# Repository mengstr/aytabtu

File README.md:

# AYTABTU

**[All Your Transistors Are Belong to Us] - A computer built from discrete parts**

This is my attempt of building a complete computer using only discrete parts like transistors, diodes, capactitors and resistors.

Just to get warmed up a bit I've started designing an UART capable of transmiting and receiving serial data in 300 bps.

I plan to make proper PCBs for the boards that I require a lot of, like memory, registers and ALU-slices, but many of the more or less one-off boards will be made on standard donut-perfboard with thru-hole parts.

## Credits
I've used, collected, gleaned, stolen, borrowed and been inspired by the information on the following web sites:

Donut pcb layout creator - [code.google.com/p/diy-layout-creator/](https://code.google.com/p/diy-layout-creator/)  
Ring counter - [vk2zay.net/article/201](http://www.vk2zay.net/article/201)  
Asymetric multivibrator - [4qdtec.com/mvibs.html](http://www.4qdtec.com/mvibs.html)  
Single cycle CPU - [eecg.toronto.edu/~moshovos/ECE243-07/...](http://www.eecg.toronto.edu/~moshovos/ECE243-07/l19-implemenation-single-cycle.html)  
Binary incrementer - [letslearncomputing.blogspot.com/2013/....](http://letslearncomputing.blogspot.com/2013/03/digital-logic-4-bit-binary-incrementer.html)  
12/8bit cpu - [usti8bit.blogspot.com](usti8bit.blogspot.com/2015_03_01_archive.html)  
8bit ttl cpu - [digitarworld.uw.hu/ttlcpu.html](http://digitarworld.uw.hu/ttlcpu.html)  
ASAP3 Computer - [pong74ls.blogspot.com/...](http://pong74ls.blogspot.com/2013/11/asap-3-almost-simple-as-possible.html)  
Tiny Tim - [northdownfarm.co.uk/rory/tim/tinytim.htm](http://www.northdownfarm.co.uk/rory/tim/tinytim.htm) 

## Links to my own resources
Link to Google Sheets for a [TX faker generator](https://docs.google.com/spreadsheets/d/1nLxUwCidM7_CYKXSP2XA_T4spadFk9zQSKAtxVXUBSM/edit?usp=sharing).

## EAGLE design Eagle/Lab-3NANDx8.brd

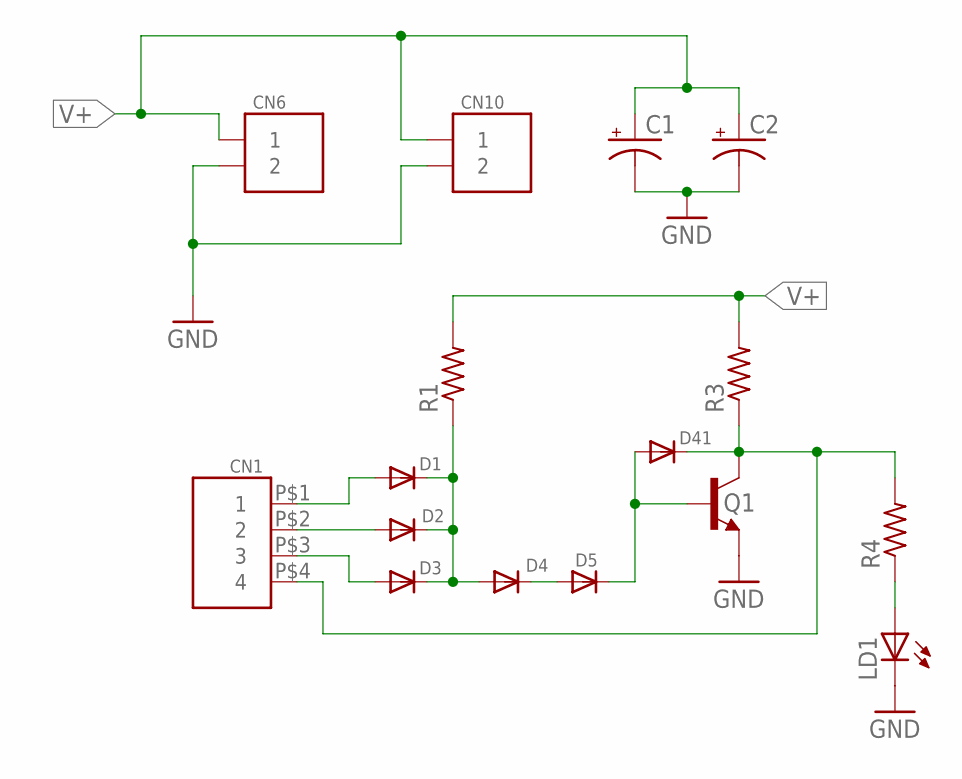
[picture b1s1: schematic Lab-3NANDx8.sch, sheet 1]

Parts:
C1, C2: CPOL-USE2.5-5; E2,5-5
CN1: HD4
CN6, CN10: HD2
D1, D2, D3, D4, D5: DIODE-6.3; DO35-6.3
D41: DIODE-7.6; DO35-7.6
LD1: LED3MM; 3MM
Q1: 2N3904-1; TO92BH
R1, R3, R4: R1/8-7.6MM; R0125-7.6

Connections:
GND: C1.-, C2.-, CN6.P$2 (2), CN10.P$2 (2), LD1.C, Q1.1 (E); also elsewhere on the board
unnamed: CN1.P$1 (1), D1.A
unnamed: CN1.P$2 (2), D2.A
unnamed: CN1.P$3 (3), D3.A
unnamed: D1.C, D2.C, D3.C, D4.A, R1.1
unnamed: D4.C, D5.A
unnamed: D5.C, D41.A, Q1.2 (B)
unnamed: LD1.A, R4.1
unnamed: CN1.P$4 (4), D41.C, Q1.3 (C), R3.1, R4.2
V+: C1.+, C2.+, CN6.P$1 (1), CN10.P$1 (1), R1.2, R3.2; also elsewhere on the board

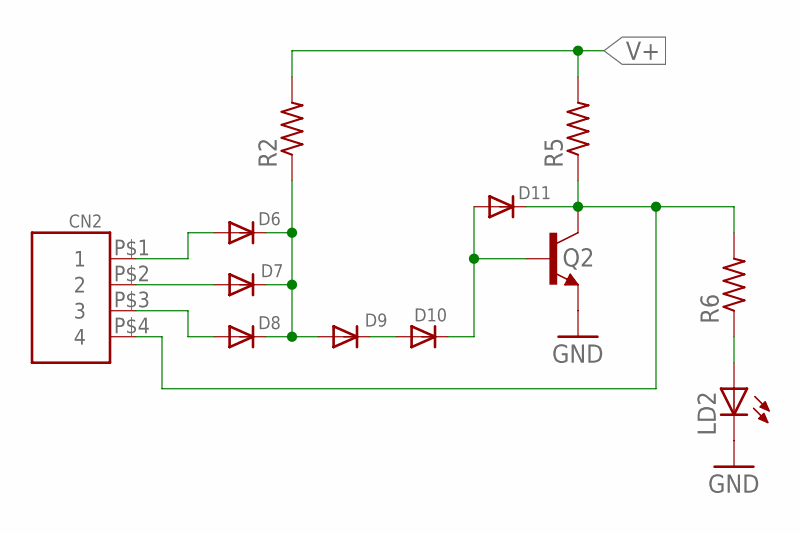
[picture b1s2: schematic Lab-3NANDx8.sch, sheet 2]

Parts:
CN2: HD4
D6, D7, D8, D9, D10: DIODE-6.3; DO35-6.3
D11: DIODE-7.6; DO35-7.6
LD2: LED3MM; 3MM
Q2: 2N3904-1; TO92BH
R2, R5, R6: R1/8-7.6MM; R0125-7.6

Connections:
GND: LD2.C, Q2.1 (E); also elsewhere on the board
unnamed: CN2.P$1 (1), D6.A
unnamed: CN2.P$2 (2), D7.A
unnamed: CN2.P$3 (3), D8.A
unnamed: D6.C, D7.C, D8.C, D9.A, R2.1
unnamed: D9.C, D10.A
unnamed: D10.C, D11.A, Q2.2 (B)
unnamed: CN2.P$4 (4), D11.C, Q2.3 (C), R5.1, R6.2
unnamed: LD2.A, R6.1
V+: R2.2, R5.2; also elsewhere on the board

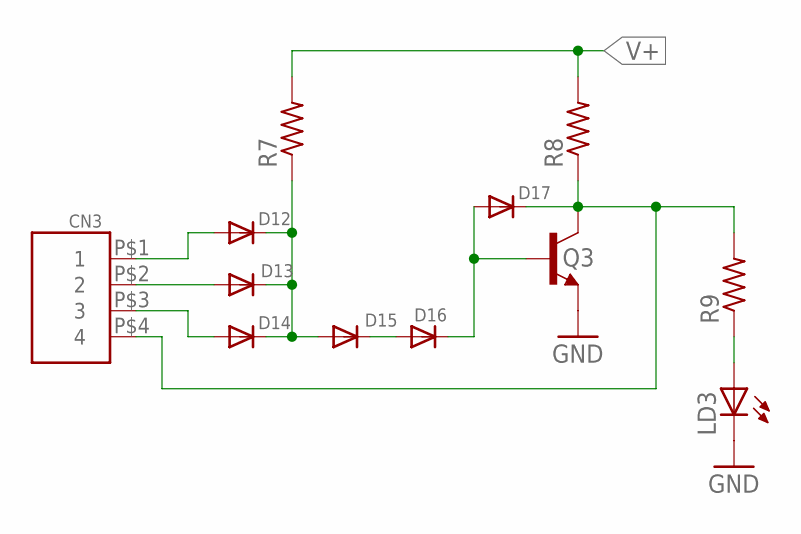
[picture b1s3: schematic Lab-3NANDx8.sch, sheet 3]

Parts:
CN3: HD4
D12, D13, D14, D15, D16: DIODE-6.3; DO35-6.3
D17: DIODE-7.6; DO35-7.6
LD3: LED3MM; 3MM
Q3: 2N3904-1; TO92BH
R7, R8, R9: R1/8-7.6MM; R0125-7.6

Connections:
GND: LD3.C, Q3.1 (E); also elsewhere on the board
unnamed: CN3.P$1 (1), D12.A
unnamed: CN3.P$2 (2), D13.A
unnamed: CN3.P$3 (3), D14.A
unnamed: D12.C, D13.C, D14.C, D15.A, R7.1
unnamed: D15.C, D16.A
unnamed: D16.C, D17.A, Q3.2 (B)
unnamed: CN3.P$4 (4), D17.C, Q3.3 (C), R8.1, R9.2
unnamed: LD3.A, R9.1
V+: R7.2, R8.2; also elsewhere on the board

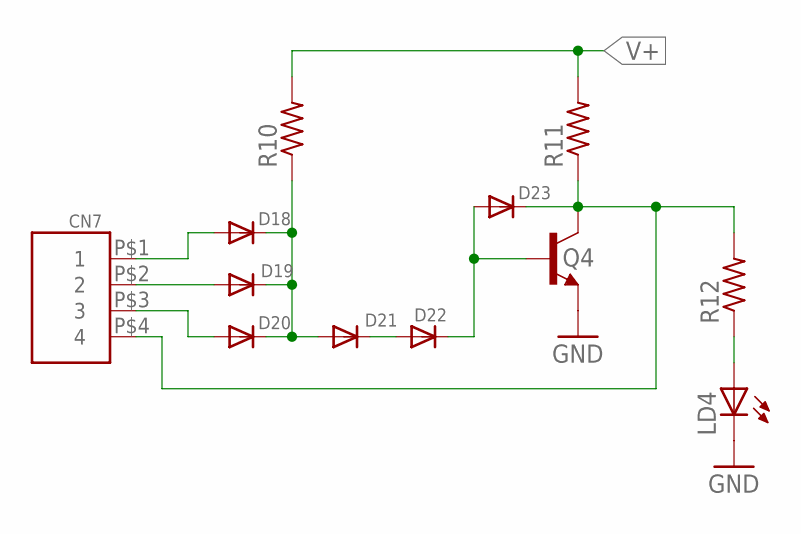
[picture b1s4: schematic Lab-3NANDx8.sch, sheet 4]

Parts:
CN7: HD4
D18, D19, D20, D21, D22: DIODE-6.3; DO35-6.3
D23: DIODE-7.6; DO35-7.6
LD4: LED3MM; 3MM
Q4: 2N3904-1; TO92BH
R10, R11, R12: R1/8-7.6MM; R0125-7.6

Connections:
GND: LD4.C, Q4.1 (E); also elsewhere on the board
unnamed: CN7.P$1 (1), D18.A
unnamed: CN7.P$2 (2), D19.A
unnamed: CN7.P$3 (3), D20.A
unnamed: D18.C, D19.C, D20.C, D21.A, R10.1
unnamed: D21.C, D22.A
unnamed: D22.C, D23.A, Q4.2 (B)
unnamed: CN7.P$4 (4), D23.C, Q4.3 (C), R11.1, R12.2
unnamed: LD4.A, R12.1
V+: R10.2, R11.2; also elsewhere on the board

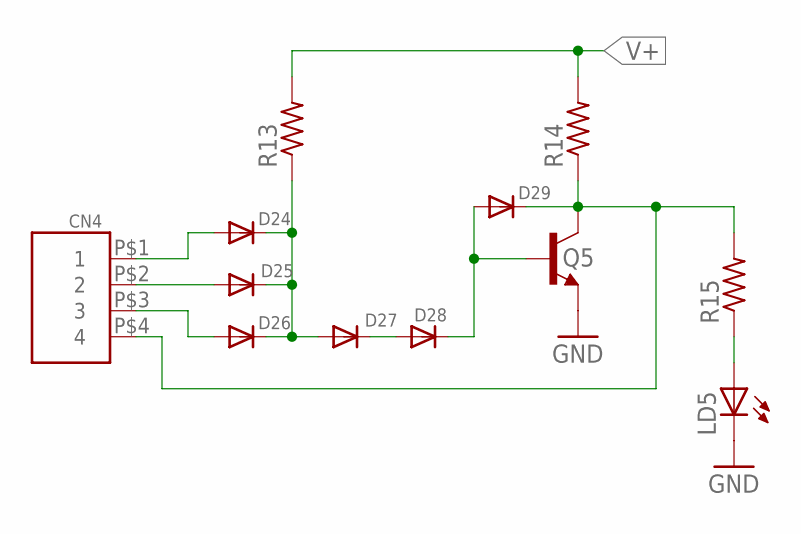
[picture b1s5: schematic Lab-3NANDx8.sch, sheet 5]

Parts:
CN4: HD4
D24, D25, D26, D27, D28: DIODE-6.3; DO35-6.3
D29: DIODE-7.6; DO35-7.6
LD5: LED3MM; 3MM
Q5: 2N3904-1; TO92BH
R13, R14, R15: R1/8-7.6MM; R0125-7.6

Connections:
GND: LD5.C, Q5.1 (E); also elsewhere on the board
unnamed: CN4.P$1 (1), D24.A
unnamed: CN4.P$2 (2), D25.A
unnamed: CN4.P$3 (3), D26.A
unnamed: D24.C, D25.C, D26.C, D27.A, R13.1
unnamed: D27.C, D28.A
unnamed: D28.C, D29.A, Q5.2 (B)
unnamed: CN4.P$4 (4), D29.C, Q5.3 (C), R14.1, R15.2
unnamed: LD5.A, R15.1
V+: R13.2, R14.2; also elsewhere on the board

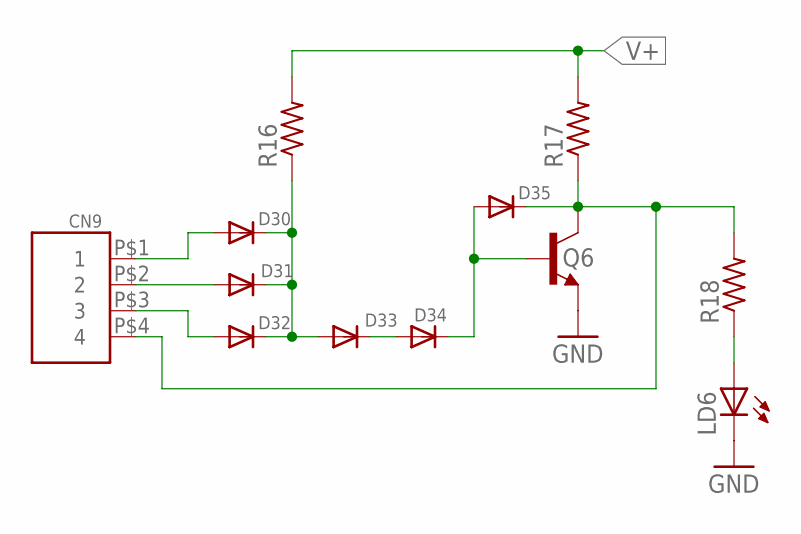
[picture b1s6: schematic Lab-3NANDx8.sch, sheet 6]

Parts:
CN9: HD4
D30, D31, D32, D33, D34: DIODE-6.3; DO35-6.3
D35: DIODE-7.6; DO35-7.6
LD6: LED3MM; 3MM
Q6: 2N3904-1; TO92BH
R16, R17, R18: R1/8-7.6MM; R0125-7.6

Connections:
GND: LD6.C, Q6.1 (E); also elsewhere on the board
unnamed: CN9.P$1 (1), D30.A
unnamed: CN9.P$2 (2), D31.A
unnamed: CN9.P$3 (3), D32.A
unnamed: D30.C, D31.C, D32.C, D33.A, R16.1
unnamed: D33.C, D34.A
unnamed: D34.C, D35.A, Q6.2 (B)
unnamed: CN9.P$4 (4), D35.C, Q6.3 (C), R17.1, R18.2
unnamed: LD6.A, R18.1
V+: R16.2, R17.2; also elsewhere on the board

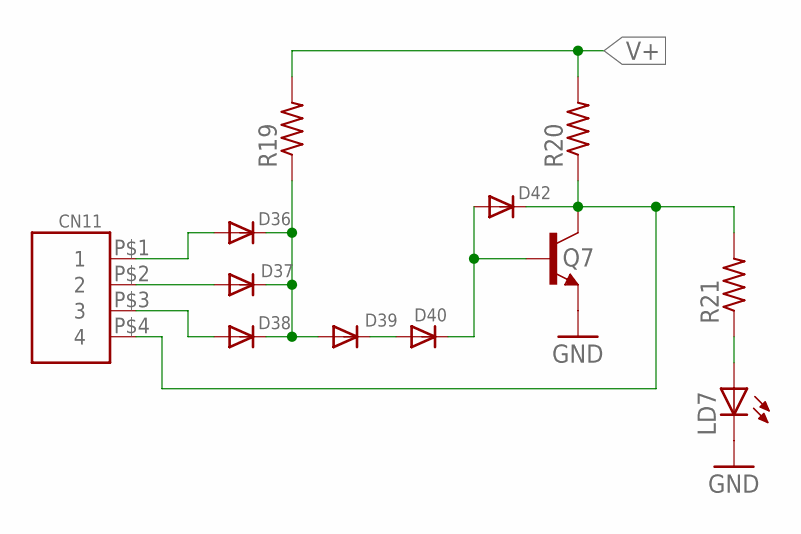
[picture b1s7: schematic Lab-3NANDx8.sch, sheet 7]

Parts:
CN11: HD4
D36, D37, D38, D39, D40: DIODE-6.3; DO35-6.3
D42: DIODE-7.6; DO35-7.6
LD7: LED3MM; 3MM
Q7: 2N3904-1; TO92BH
R19, R20, R21: R1/8-7.6MM; R0125-7.6

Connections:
GND: LD7.C, Q7.1 (E); also elsewhere on the board
unnamed: CN11.P$1 (1), D36.A
unnamed: CN11.P$2 (2), D37.A
unnamed: CN11.P$3 (3), D38.A
unnamed: D36.C, D37.C, D38.C, D39.A, R19.1
unnamed: D39.C, D40.A
unnamed: D40.C, D42.A, Q7.2 (B)
unnamed: CN11.P$4 (4), D42.C, Q7.3 (C), R20.1, R21.2
unnamed: LD7.A, R21.1
V+: R19.2, R20.2; also elsewhere on the board

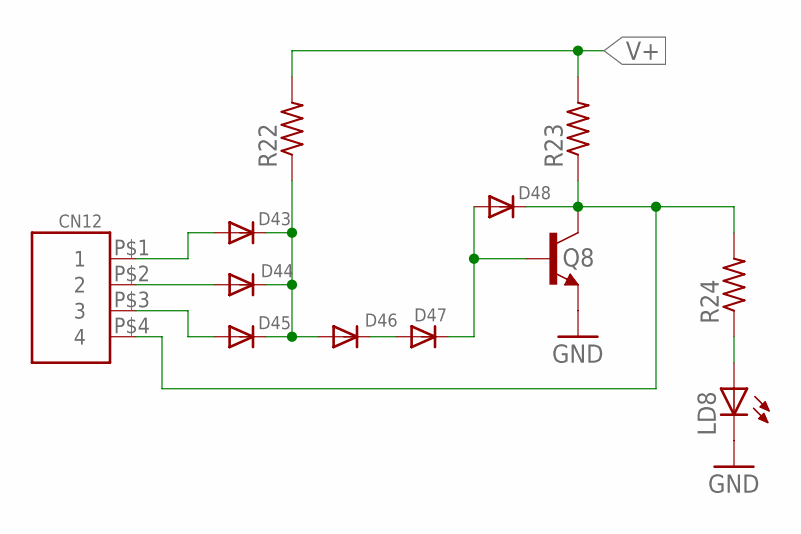
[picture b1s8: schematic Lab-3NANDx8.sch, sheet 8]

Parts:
CN12: HD4
D43, D44, D45, D46, D47: DIODE-6.3; DO35-6.3
D48: DIODE-7.6; DO35-7.6
LD8: LED3MM; 3MM
Q8: 2N3904-1; TO92BH
R22, R23, R24: R1/8-7.6MM; R0125-7.6

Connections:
GND: LD8.C, Q8.1 (E); also elsewhere on the board
unnamed: CN12.P$1 (1), D43.A
unnamed: CN12.P$2 (2), D44.A
unnamed: CN12.P$3 (3), D45.A
unnamed: D43.C, D44.C, D45.C, D46.A, R22.1
unnamed: D46.C, D47.A
unnamed: D47.C, D48.A, Q8.2 (B)
unnamed: CN12.P$4 (4), D48.C, Q8.3 (C), R23.1, R24.2
unnamed: LD8.A, R24.1
V+: R22.2, R23.2; also elsewhere on the board

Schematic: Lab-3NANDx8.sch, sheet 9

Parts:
CN5: HD4
D49, D50, D51, D52, D53: DIODE-6.3; DO35-6.3
D54: DIODE-7.6; DO35-7.6
LD9: LED3MM; 3MM
Q9: 2N3904-1; TO92BH
R25, R26, R27: R1/8-7.6MM; R0125-7.6

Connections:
GND: LD9.C, Q9.1 (E); also elsewhere on the board
unnamed: CN5.P$1 (1), D49.A
unnamed: CN5.P$2 (2), D50.A
unnamed: CN5.P$3 (3), D51.A
unnamed: D49.C, D50.C, D51.C, D52.A, R25.1
unnamed: D52.C, D53.A
unnamed: D53.C, D54.A, Q9.2 (B)
unnamed: CN5.P$4 (4), D54.C, Q9.3 (C), R26.1, R27.2
unnamed: LD9.A, R27.1
V+: R25.2, R26.2; also elsewhere on the board

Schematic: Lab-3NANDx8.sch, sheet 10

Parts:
CN14: HD4
D55, D56, D57, D58, D59: DIODE-6.3; DO35-6.3
D60: DIODE-7.6; DO35-7.6
LD10: LED3MM; 3MM
Q10: 2N3904-1; TO92BH
R28, R29, R30: R1/8-7.6MM; R0125-7.6

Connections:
GND: LD10.C, Q10.1 (E); also elsewhere on the board
unnamed: CN14.P$1 (1), D55.A
unnamed: CN14.P$2 (2), D56.A
unnamed: CN14.P$3 (3), D57.A
unnamed: D55.C, D56.C, D57.C, D58.A, R28.1
unnamed: D58.C, D59.A
unnamed: D59.C, D60.A, Q10.2 (B)
unnamed: CN14.P$4 (4), D60.C, Q10.3 (C), R29.1, R30.2
unnamed: LD10.A, R30.1
V+: R28.2, R29.2; also elsewhere on the board

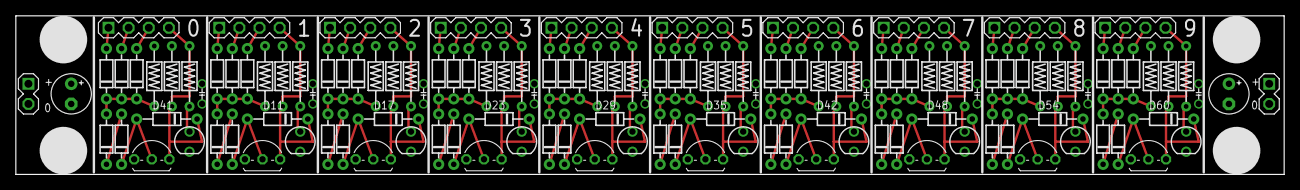
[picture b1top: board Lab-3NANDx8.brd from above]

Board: 2 copper layers, 160.0 x 20.0 mm, 124 parts (0 on the bottom side), 82 nets.

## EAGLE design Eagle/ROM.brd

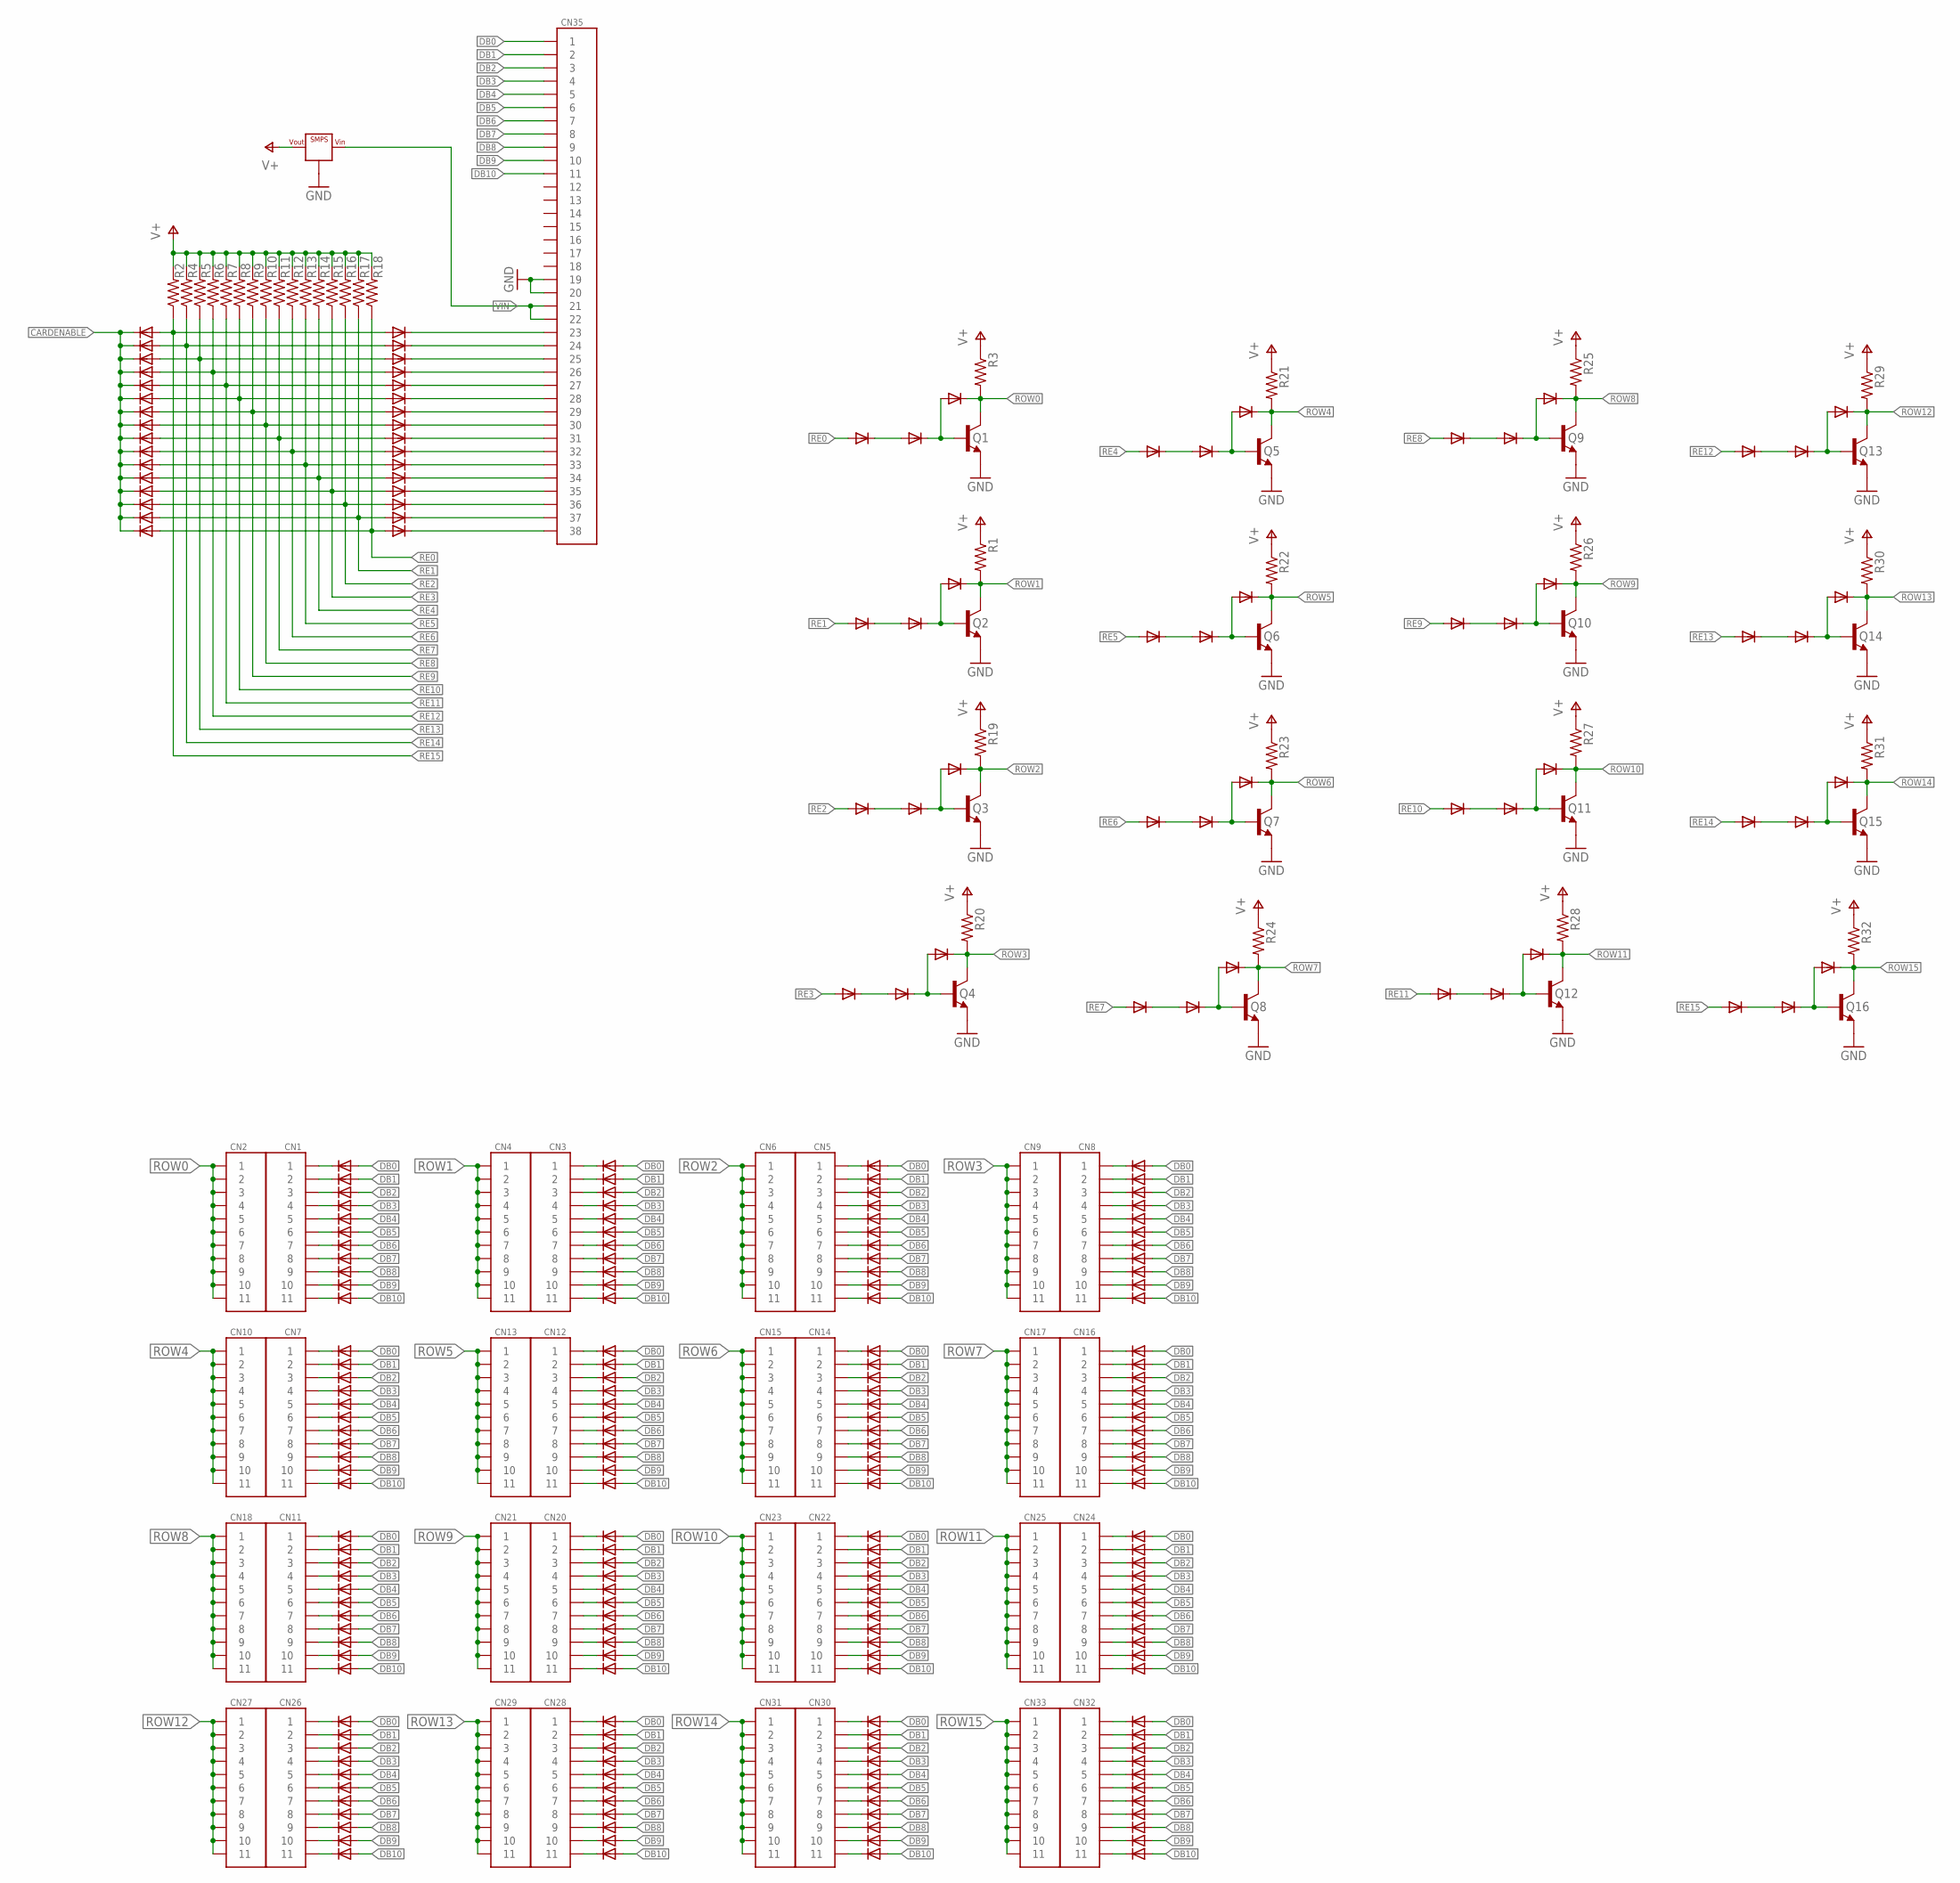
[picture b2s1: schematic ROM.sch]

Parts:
CN1, CN2, CN3, CN4, CN5, CN6, CN7, CN8, CN9, CN10, CN11, CN12, CN13, CN14, CN15, CN16, CN17, CN18, CN20, CN21, CN22, CN23, CN24, CN25, CN26, CN27, CN28, CN29, CN30, CN31, CN32, CN33: HD11
CN35: HD38-HP; HD38-HOLEPAD
D1, D2, D3, D4, D5, D6, D7, D8, D9, D10, D11, D12, D13, D14, D15, D16, D17, D18, D19, D20, D21, D22, D23, D24, D25, D26, D27, D28, D29, D30, D31, D32, D33, D34, D35, D36, D37, D38, D39, D40, D41, D42, D43, D44, D45, D46, D47, D48, D49, D50, D51, D52, D53, D54, D55, D56, D57, D58, D59, D60, D61, D62, D63, D64, D65, D66, D67, D68, D69, D70, D71, D72, D73, D74, D75, D76, D77, D78, D79, D80, D81, D82, D83, D84, D85, D86, D87, D88, D89, D90, D91, D92, D93, D94, D95, D96, D97, D98, D99, D100, D101, D102, D103, D104, D105, D106, D107, D108, D109, D110, D111, D112, D113, D114, D115, D116, D117, D118, D119, D120, D121, D122, D123, D124, D125, D126, D127, D128, D129, D130, D131, D132, D133, D134, D135, D136, D137, D138, D139, D140, D141, D142, D143, D144, D145, D146, D147, D148, D149, D150, D151, D152, D153, D154, D155, D156, D157, D158, D159, D160, D161, D162, D163, D164, D165, D166, D167, D168, D169, D170, D171, D172, D173, D174, D175, D176: DIODE-6.3; DO35-6.3
D177, D178, D179, D180, D181, D182, D183, D184, D185, D186, D187, D188, D189, D190, D191, D192, D193, D194, D195, D196, D197, D198, D199, D200, D201, D202, D203, D204, D205, D206, D207, D208, D209, D210, D211, D212, D213, D214, D215, D216, D217, D218, D219, D220, D221, D222, D223, D224, D225, D226, D227, D228, D229, D230, D231, D232, D233, D234, D235, D236, D237, D238, D239, D240, D241, D242, D243, D244, D245, D246, D247, D248, D249, D250, D251, D252, D253, D254, D255, D256: DIODE-5.08; DO35-5.08
Q1, Q2, Q3, Q4, Q5, Q6, Q7, Q8, Q9, Q10, Q11, Q12, Q13, Q14, Q15, Q16: BC547-STRAIGHT; TO92-S-CBE
R1, R2, R3, R4, R5, R6, R7, R8, R9, R10, R11, R12, R13, R14, R15, R16, R17, R18, R19, R20, R21, R22, R23, R24, R25, R26, R27, R28, R29, R30, R31, R32: R1/8-6MM; R0125-6.3
VR1: SMPS; BUCK1722

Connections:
CARDENABLE: D182.C, D183.C, D184.C, D185.C, D186.C, D187.C, D188.C, D189.C, D190.C, D191.C, D192.C, D193.C, D194.C, D195.C, D196.C, D197.C
DB0: CN35.P1@1 (1), CN35.P1@2 (1), D1.A, D12.A, D23.A, D34.A, D45.A, D56.A, D67.A, D78.A, D89.A, D100.A, D111.A, D122.A, D133.A, D144.A, D155.A, D166.A
DB1: CN35.P2@1 (2), CN35.P2@2 (2), D2.A, D13.A, D24.A, D35.A, D46.A, D57.A, D68.A, D79.A, D90.A, D101.A, D112.A, D123.A, D134.A, D145.A, D156.A, D167.A
DB2: CN35.P3@1 (3), CN35.P3@2 (3), D3.A, D14.A, D25.A, D36.A, D47.A, D58.A, D69.A, D80.A, D91.A, D102.A, D113.A, D124.A, D135.A, D146.A, D157.A, D168.A
DB3: CN35.P4@1 (4), CN35.P4@2 (4), D4.A, D15.A, D26.A, D37.A, D48.A, D59.A, D70.A, D81.A, D92.A, D103.A, D114.A, D125.A, D136.A, D147.A, D158.A, D169.A
DB4: CN35.P5@1 (5), CN35.P5@2 (5), D5.A, D16.A, D27.A, D38.A, D49.A, D60.A, D71.A, D82.A, D93.A, D104.A, D115.A, D126.A, D137.A, D148.A, D159.A, D170.A
DB5: CN35.P6@1 (6), CN35.P6@2 (6), D6.A, D17.A, D28.A, D39.A, D50.A, D61.A, D72.A, D83.A, D94.A, D105.A, D116.A, D127.A, D138.A, D149.A, D160.A, D171.A
DB6: CN35.P7@1 (7), CN35.P7@2 (7), D7.A, D18.A, D29.A, D40.A, D51.A, D62.A, D73.A, D84.A, D95.A, D106.A, D117.A, D128.A, D139.A, D150.A, D161.A, D172.A
DB7: CN35.P8@1 (8), CN35.P8@2 (8), D8.A, D19.A, D30.A, D41.A, D52.A, D63.A, D74.A, D85.A, D96.A, D107.A, D118.A, D129.A, D140.A, D151.A, D162.A, D173.A
DB8: CN35.P9@1 (9), CN35.P9@2 (9), D9.A, D20.A, D31.A, D42.A, D53.A, D64.A, D75.A, D86.A, D97.A, D108.A, D119.A, D130.A, D141.A, D152.A, D163.A, D174.A
DB9: CN35.P10@1 (10), CN35.P10@2 (10), D10.A, D21.A, D32.A, D43.A, D54.A, D65.A, D76.A, D87.A, D98.A, D109.A, D120.A, D131.A, D142.A, D153.A, D164.A, D175.A
DB10: CN35.P11@1 (11), CN35.P11@2 (11), D11.A, D22.A, D33.A, D44.A, D55.A, D66.A, D77.A, D88.A, D99.A, D110.A, D121.A, D132.A, D143.A, D154.A, D165.A, D176.A
GND: CN35.P19@1 (19), CN35.P19@2 (19), CN35.P20@1 (20), CN35.P20@2 (20), Q1.E, Q2.E, Q3.E, Q4.E, Q5.E, Q6.E, Q7.E, Q8.E, Q9.E, Q10.E, Q11.E, Q12.E, Q13.E, Q14.E, Q15.E, Q16.E, VR1.GND@1 (GND), VR1.GND@2 (GND), VR1.GND@3 (GND), VR1.GND@4 (GND)
unnamed: CN1.P$1 (1), D1.C
unnamed: CN1.P$2 (2), D2.C
unnamed: CN1.P$3 (3), D3.C
unnamed: CN1.P$4 (4), D4.C
unnamed: CN1.P$5 (5), D5.C
unnamed: CN1.P$6 (6), D6.C
unnamed: CN1.P$7 (7), D7.C
unnamed: CN1.P$8 (8), D8.C
unnamed: CN1.P$9 (9), D9.C
unnamed: CN1.P$10 (10), D10.C
unnamed: CN1.P$11 (11), D11.C
unnamed: CN3.P$1 (1), D12.C
unnamed: CN3.P$2 (2), D13.C
unnamed: CN3.P$3 (3), D14.C
unnamed: CN3.P$4 (4), D15.C
unnamed: CN3.P$5 (5), D16.C
unnamed: CN3.P$6 (6), D17.C
unnamed: CN3.P$7 (7), D18.C
unnamed: CN3.P$8 (8), D19.C
unnamed: CN3.P$9 (9), D20.C
unnamed: CN3.P$10 (10), D21.C
unnamed: CN3.P$11 (11), D22.C
unnamed: CN5.P$1 (1), D23.C
unnamed: CN5.P$2 (2), D24.C
unnamed: CN5.P$3 (3), D25.C
unnamed: CN5.P$4 (4), D26.C
unnamed: CN5.P$5 (5), D27.C
unnamed: CN5.P$6 (6), D28.C
unnamed: CN5.P$7 (7), D29.C
unnamed: CN5.P$8 (8), D30.C
unnamed: CN5.P$9 (9), D31.C
unnamed: CN5.P$10 (10), D32.C
unnamed: CN5.P$11 (11), D33.C
unnamed: CN8.P$1 (1), D34.C
unnamed: CN8.P$2 (2), D35.C
unnamed: CN8.P$3 (3), D36.C
unnamed: CN8.P$4 (4), D37.C
unnamed: CN8.P$5 (5), D38.C
unnamed: CN8.P$6 (6), D39.C
unnamed: CN8.P$7 (7), D40.C
unnamed: CN8.P$8 (8), D41.C
unnamed: CN8.P$9 (9), D42.C
unnamed: CN8.P$10 (10), D43.C
unnamed: CN8.P$11 (11), D44.C
unnamed: CN7.P$1 (1), D45.C
unnamed: CN7.P$2 (2), D46.C
unnamed: CN7.P$3 (3), D47.C
unnamed: CN7.P$4 (4), D48.C
unnamed: CN7.P$5 (5), D49.C
unnamed: CN7.P$6 (6), D50.C
unnamed: CN7.P$7 (7), D51.C
unnamed: CN7.P$8 (8), D52.C
unnamed: CN7.P$9 (9), D53.C
unnamed: CN7.P$10 (10), D54.C
unnamed: CN7.P$11 (11), D55.C
unnamed: CN12.P$1 (1), D56.C
unnamed: CN12.P$2 (2), D57.C
unnamed: CN12.P$3 (3), D58.C
unnamed: CN12.P$4 (4), D59.C
unnamed: CN12.P$5 (5), D60.C
unnamed: CN12.P$6 (6), D61.C
unnamed: CN12.P$7 (7), D62.C
unnamed: CN12.P$8 (8), D63.C
unnamed: CN12.P$9 (9), D64.C
unnamed: CN12.P$10 (10), D65.C
unnamed: CN12.P$11 (11), D66.C
unnamed: CN14.P$1 (1), D67.C
unnamed: CN14.P$2 (2), D68.C
unnamed: CN14.P$3 (3), D69.C
unnamed: CN14.P$4 (4), D70.C
unnamed: CN14.P$5 (5), D71.C
unnamed: CN14.P$6 (6), D72.C
unnamed: CN14.P$7 (7), D73.C
unnamed: CN14.P$8 (8), D74.C
unnamed: CN14.P$9 (9), D75.C
unnamed: CN14.P$10 (10), D76.C
unnamed: CN14.P$11 (11), D77.C
unnamed: CN16.P$1 (1), D78.C
unnamed: CN16.P$2 (2), D79.C
unnamed: CN16.P$3 (3), D80.C
unnamed: CN16.P$4 (4), D81.C
unnamed: CN16.P$5 (5), D82.C
unnamed: CN16.P$6 (6), D83.C
unnamed: CN16.P$7 (7), D84.C
unnamed: CN16.P$8 (8), D85.C
unnamed: CN16.P$9 (9), D86.C
unnamed: CN16.P$10 (10), D87.C
unnamed: CN16.P$11 (11), D88.C
unnamed: CN11.P$1 (1), D89.C
unnamed: CN11.P$2 (2), D90.C
unnamed: CN11.P$3 (3), D91.C
unnamed: CN11.P$4 (4), D92.C
unnamed: CN11.P$5 (5), D93.C
unnamed: CN11.P$6 (6), D94.C
unnamed: CN11.P$7 (7), D95.C
unnamed: CN11.P$8 (8), D96.C
unnamed: CN11.P$9 (9), D97.C
unnamed: CN11.P$10 (10), D98.C
unnamed: CN11.P$11 (11), D99.C
unnamed: CN20.P$1 (1), D100.C
unnamed: CN20.P$2 (2), D101.C
unnamed: CN20.P$3 (3), D102.C
unnamed: CN20.P$4 (4), D103.C
unnamed: CN20.P$5 (5), D104.C
unnamed: CN20.P$6 (6), D105.C
unnamed: CN20.P$7 (7), D106.C
unnamed: CN20.P$8 (8), D107.C
unnamed: CN20.P$9 (9), D108.C
unnamed: CN20.P$10 (10), D109.C
unnamed: CN20.P$11 (11), D110.C
unnamed: CN22.P$1 (1), D111.C
unnamed: CN22.P$2 (2), D112.C
unnamed: CN22.P$3 (3), D113.C
unnamed: CN22.P$4 (4), D114.C
unnamed: CN22.P$5 (5), D115.C
unnamed: CN22.P$6 (6), D116.C
unnamed: CN22.P$7 (7), D117.C
unnamed: CN22.P$8 (8), D118.C
unnamed: CN22.P$9 (9), D119.C
unnamed: CN22.P$10 (10), D120.C
unnamed: CN22.P$11 (11), D121.C
unnamed: CN24.P$1 (1), D122.C
unnamed: CN24.P$2 (2), D123.C
unnamed: CN24.P$3 (3), D124.C
unnamed: CN24.P$4 (4), D125.C
unnamed: CN24.P$5 (5), D126.C
unnamed: CN24.P$6 (6), D127.C
unnamed: CN24.P$7 (7), D128.C
unnamed: CN24.P$8 (8), D129.C
unnamed: CN24.P$9 (9), D130.C
unnamed: CN24.P$10 (10), D131.C
unnamed: CN24.P$11 (11), D132.C
unnamed: CN26.P$1 (1), D133.C
unnamed: CN26.P$2 (2), D134.C
unnamed: CN26.P$3 (3), D135.C
unnamed: CN26.P$4 (4), D136.C
unnamed: CN26.P$5 (5), D137.C
unnamed: CN26.P$6 (6), D138.C
unnamed: CN26.P$7 (7), D139.C
unnamed: CN26.P$8 (8), D140.C
unnamed: CN26.P$9 (9), D141.C
unnamed: CN26.P$10 (10), D142.C
unnamed: CN26.P$11 (11), D143.C
unnamed: CN28.P$1 (1), D144.C
unnamed: CN28.P$2 (2), D145.C
unnamed: CN28.P$3 (3), D146.C
unnamed: CN28.P$4 (4), D147.C
unnamed: CN28.P$5 (5), D148.C
unnamed: CN28.P$6 (6), D149.C
unnamed: CN28.P$7 (7), D150.C
unnamed: CN28.P$8 (8), D151.C
unnamed: CN28.P$9 (9), D152.C
unnamed: CN28.P$10 (10), D153.C
unnamed: CN28.P$11 (11), D154.C
unnamed: CN30.P$1 (1), D155.C
unnamed: CN30.P$2 (2), D156.C
unnamed: CN30.P$3 (3), D157.C
unnamed: CN30.P$4 (4), D158.C
unnamed: CN30.P$5 (5), D159.C
unnamed: CN30.P$6 (6), D160.C
unnamed: CN30.P$7 (7), D161.C
unnamed: CN30.P$8 (8), D162.C
unnamed: CN30.P$9 (9), D163.C
unnamed: CN30.P$10 (10), D164.C
unnamed: CN30.P$11 (11), D165.C
unnamed: CN32.P$1 (1), D166.C
unnamed: CN32.P$2 (2), D167.C
unnamed: CN32.P$3 (3), D168.C
unnamed: CN32.P$4 (4), D169.C
unnamed: CN32.P$5 (5), D170.C
unnamed: CN32.P$6 (6), D171.C
unnamed: CN32.P$7 (7), D172.C
unnamed: CN32.P$8 (8), D173.C
unnamed: CN32.P$9 (9), D174.C
unnamed: CN32.P$10 (10), D175.C
unnamed: CN32.P$11 (11), D176.C
unnamed: D215.A, D216.C
unnamed: D177.C, D181.A, Q1.B
unnamed: D177.A, D178.C
unnamed: D212.C, D214.A, Q2.B
unnamed: D212.A, D213.C
unnamed: D215.C, D217.A, Q3.B
unnamed: D242.A, D243.C
unnamed: D218.C, D220.A, Q4.B
unnamed: D218.A, D219.C
unnamed: D221.C, D223.A, Q5.B
unnamed: D221.A, D222.C
unnamed: D224.C, D226.A, Q6.B
unnamed: D224.A, D225.C
unnamed: D227.C, D229.A, Q7.B
unnamed: D227.A, D228.C
unnamed: D230.C, D232.A, Q8.B
unnamed: D230.A, D231.C
unnamed: D233.C, D235.A, Q9.B
unnamed: D233.A, D234.C
unnamed: D236.C, D238.A, Q10.B
unnamed: D239.C, D241.A, Q11.B
unnamed: D239.A, D240.C
unnamed: D242.C, D244.A, Q12.B
unnamed: D251.A, D252.C
unnamed: D245.C, D247.A, Q13.B
unnamed: D236.A, D237.C
unnamed: D248.C, D250.A, Q14.B
unnamed: D245.A, D246.C
unnamed: D251.C, D253.A, Q15.B
unnamed: D248.A, D249.C
unnamed: D254.C, D256.A, Q16.B
unnamed: D254.A, D255.C
RE0: D178.A, D197.A, D211.A, R18.1
RE1: D196.A, D210.A, D213.A, R17.1
RE2: D195.A, D209.A, D216.A, R16.1
RE3: D194.A, D208.A, D219.A, R15.1
RE4: D193.A, D207.A, D222.A, R14.1
RE5: D192.A, D206.A, D225.A, R13.1
RE6: D191.A, D205.A, D228.A, R12.1
RE7: D190.A, D204.A, D231.A, R11.1
RE8: D189.A, D203.A, D234.A, R10.1
RE9: D188.A, D202.A, D237.A, R9.1
RE10: D187.A, D201.A, D240.A, R8.1
RE11: D186.A, D200.A, D243.A, R7.1
RE12: D185.A, D199.A, D246.A, R6.1
RE13: D184.A, D198.A, D249.A, R5.1
RE14: D180.A, D183.A, D252.A, R4.1
RE15: D179.A, D182.A, D255.A, R2.1
ROW0: CN2.P$1 (1), CN2.P$2 (2), CN2.P$3 (3), CN2.P$4 (4), CN2.P$5 (5), CN2.P$6 (6), CN2.P$7 (7), CN2.P$8 (8), CN2.P$9 (9), CN2.P$10 (10), CN2.P$11 (11), D181.C, Q1.C, R3.2
ROW1: CN4.P$1 (1), CN4.P$2 (2), CN4.P$3 (3), CN4.P$4 (4), CN4.P$5 (5), CN4.P$6 (6), CN4.P$7 (7), CN4.P$8 (8), CN4.P$9 (9), CN4.P$10 (10), CN4.P$11 (11), D214.C, Q2.C, R1.2
ROW2: CN6.P$1 (1), CN6.P$2 (2), CN6.P$3 (3), CN6.P$4 (4), CN6.P$5 (5), CN6.P$6 (6), CN6.P$7 (7), CN6.P$8 (8), CN6.P$9 (9), CN6.P$10 (10), CN6.P$11 (11), D217.C, Q3.C, R19.2
ROW3: CN9.P$1 (1), CN9.P$2 (2), CN9.P$3 (3), CN9.P$4 (4), CN9.P$5 (5), CN9.P$6 (6), CN9.P$7 (7), CN9.P$8 (8), CN9.P$9 (9), CN9.P$10 (10), CN9.P$11 (11), D220.C, Q4.C, R20.2
ROW4: CN10.P$1 (1), CN10.P$2 (2), CN10.P$3 (3), CN10.P$4 (4), CN10.P$5 (5), CN10.P$6 (6), CN10.P$7 (7), CN10.P$8 (8), CN10.P$9 (9), CN10.P$10 (10), CN10.P$11 (11), D223.C, Q5.C, R21.2
ROW5: CN13.P$1 (1), CN13.P$2 (2), CN13.P$3 (3), CN13.P$4 (4), CN13.P$5 (5), CN13.P$6 (6), CN13.P$7 (7), CN13.P$8 (8), CN13.P$9 (9), CN13.P$10 (10), CN13.P$11 (11), D226.C, Q6.C, R22.2
ROW6: CN15.P$1 (1), CN15.P$2 (2), CN15.P$3 (3), CN15.P$4 (4), CN15.P$5 (5), CN15.P$6 (6), CN15.P$7 (7), CN15.P$8 (8), CN15.P$9 (9), CN15.P$10 (10), CN15.P$11 (11), D229.C, Q7.C, R23.2
ROW7: CN17.P$1 (1), CN17.P$2 (2), CN17.P$3 (3), CN17.P$4 (4), CN17.P$5 (5), CN17.P$6 (6), CN17.P$7 (7), CN17.P$8 (8), CN17.P$9 (9), CN17.P$10 (10), CN17.P$11 (11), D232.C, Q8.C, R24.2
ROW8: CN18.P$1 (1), CN18.P$2 (2), CN18.P$3 (3), CN18.P$4 (4), CN18.P$5 (5), CN18.P$6 (6), CN18.P$7 (7), CN18.P$8 (8), CN18.P$9 (9), CN18.P$10 (10), CN18.P$11 (11), D235.C, Q9.C, R25.2
ROW9: CN21.P$1 (1), CN21.P$2 (2), CN21.P$3 (3), CN21.P$4 (4), CN21.P$5 (5), CN21.P$6 (6), CN21.P$7 (7), CN21.P$8 (8), CN21.P$9 (9), CN21.P$10 (10), CN21.P$11 (11), D238.C, Q10.C, R26.2
ROW10: CN23.P$1 (1), CN23.P$2 (2), CN23.P$3 (3), CN23.P$4 (4), CN23.P$5 (5), CN23.P$6 (6), CN23.P$7 (7), CN23.P$8 (8), CN23.P$9 (9), CN23.P$10 (10), CN23.P$11 (11), D241.C, Q11.C, R27.2
ROW11: CN25.P$1 (1), CN25.P$2 (2), CN25.P$3 (3), CN25.P$4 (4), CN25.P$5 (5), CN25.P$6 (6), CN25.P$7 (7), CN25.P$8 (8), CN25.P$9 (9), CN25.P$10 (10), CN25.P$11 (11), D244.C, Q12.C, R28.2
ROW12: CN27.P$1 (1), CN27.P$2 (2), CN27.P$3 (3), CN27.P$4 (4), CN27.P$5 (5), CN27.P$6 (6), CN27.P$7 (7), CN27.P$8 (8), CN27.P$9 (9), CN27.P$10 (10), CN27.P$11 (11), D247.C, Q13.C, R29.2
ROW13: CN29.P$1 (1), CN29.P$2 (2), CN29.P$3 (3), CN29.P$4 (4), CN29.P$5 (5), CN29.P$6 (6), CN29.P$7 (7), CN29.P$8 (8), CN29.P$9 (9), CN29.P$10 (10), CN29.P$11 (11), D250.C, Q14.C, R30.2
ROW14: CN31.P$1 (1), CN31.P$2 (2), CN31.P$3 (3), CN31.P$4 (4), CN31.P$5 (5), CN31.P$6 (6), CN31.P$7 (7), CN31.P$8 (8), CN31.P$9 (9), CN31.P$10 (10), CN31.P$11 (11), D253.C, Q15.C, R31.2
ROW15: CN33.P$1 (1), CN33.P$2 (2), CN33.P$3 (3), CN33.P$4 (4), CN33.P$5 (5), CN33.P$6 (6), CN33.P$7 (7), CN33.P$8 (8), CN33.P$9 (9), CN33.P$10 (10), CN33.P$11 (11), D256.C, Q16.C, R32.2
SEL0: CN35.P23@1 (23), CN35.P23@2 (23), D179.C
SEL1: CN35.P24@1 (24), CN35.P24@2 (24), D180.C
SEL2: CN35.P25@1 (25), CN35.P25@2 (25), D198.C
SEL3: CN35.P26@1 (26), CN35.P26@2 (26), D199.C
SEL4: CN35.P27@1 (27), CN35.P27@2 (27), D200.C
SEL5: CN35.P28@1 (28), CN35.P28@2 (28), D201.C
SEL6: CN35.P29@1 (29), CN35.P29@2 (29), D202.C
SEL7: CN35.P30@1 (30), CN35.P30@2 (30), D203.C
SEL8: CN35.P31@1 (31), CN35.P31@2 (31), D204.C
SEL9: CN35.P32@1 (32), CN35.P32@2 (32), D205.C
SEL10: CN35.P33@1 (33), CN35.P33@2 (33), D206.C
SEL11: CN35.P34@1 (34), CN35.P34@2 (34), D207.C
SEL12: CN35.P35@1 (35), CN35.P35@2 (35), D208.C
SEL13: CN35.P36@1 (36), CN35.P36@2 (36), D209.C
SEL14: CN35.P37@1 (37), CN35.P37@2 (37), D210.C
SEL15: CN35.P38@1 (38), CN35.P38@2 (38), D211.C
V+: R1.1, R2.2, R3.1, R4.2, R5.2, R6.2, R7.2, R8.2, R9.2, R10.2, R11.2, R12.2, R13.2, R14.2, R15.2, R16.2, R17.2, R18.2, R19.1, R20.1, R21.1, R22.1, R23.1, R24.1, R25.1, R26.1, R27.1, R28.1, R29.1, R30.1, R31.1, R32.1, VR1.OUT@1 (VOUT), VR1.OUT@2 (VOUT)
VIN: CN35.P21@1 (21), CN35.P21@2 (21), CN35.P22@1 (22), CN35.P22@2 (22), VR1.IN@1 (VIN), VR1.IN@2 (VIN)
